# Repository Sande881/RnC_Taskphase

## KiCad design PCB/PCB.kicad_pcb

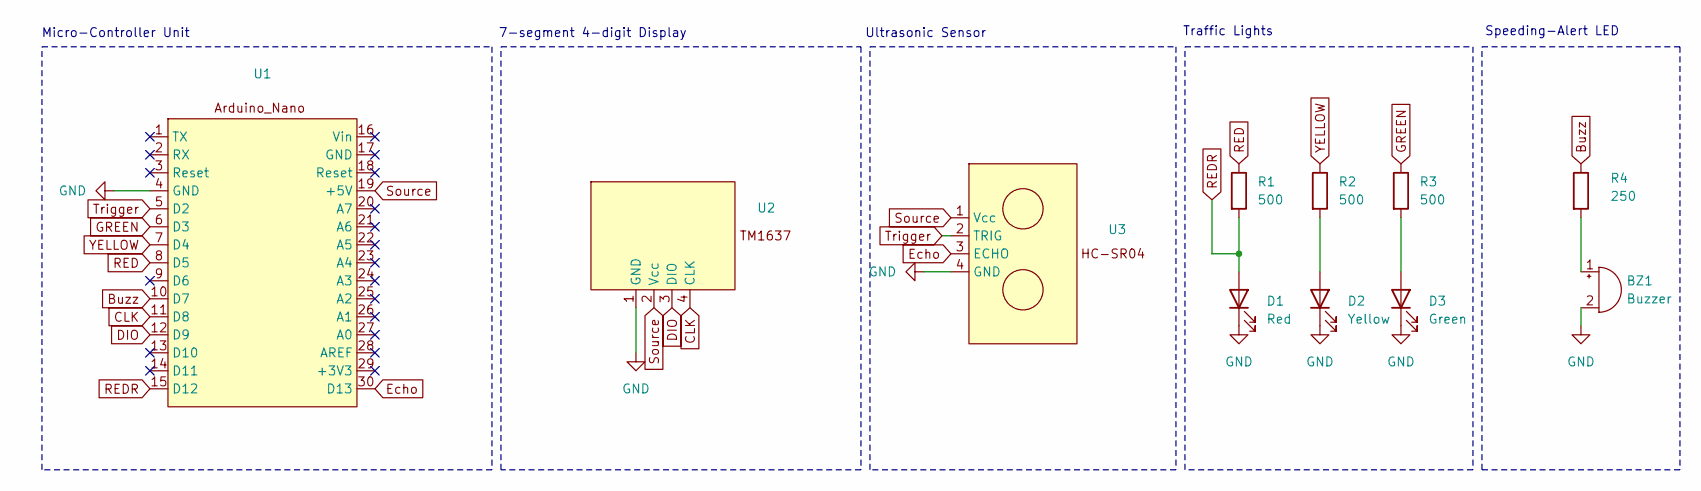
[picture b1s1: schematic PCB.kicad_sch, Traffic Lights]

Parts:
BZ1: Buzzer; Buzzer_12x9.5RM7.6
D1: Red; LED_D3.0mm_Horizontal_O1.27mm_Z2.0mm_IRGrey
D2: Yellow; LED_D3.0mm_Horizontal_O1.27mm_Z2.0mm_IRGrey
D3: Green; LED_D3.0mm_Horizontal_O1.27mm_Z2.0mm_IRGrey
R1, R2, R3: 500; R_Axial_DIN0918_L18.0mm_D9.0mm_P22.86mm_Horizontal
R4: 250; R_Axial_DIN0918_L18.0mm_D9.0mm_P22.86mm_Horizontal
U1: Arduino_Nano
U2: TM1637
U3: HC-SR04

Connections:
Buzz: R4.1, U1.10 (D7)
CLK: U1.11 (D8), U2.4 (CLK)
DIO: U1.12 (D9), U2.3 (DIO)
Echo: U1.30 (D13), U3.3 (ECHO)
GND: BZ1.2 (-), D1.1 (K), D2.1 (K), D3.1 (K), U1.4 (GND), U2.1 (GND), U3.4 (GND)
GREEN: R3.1, U1.6 (D3)
unnamed: BZ1.1 (+), R4.2
unnamed: D2.2 (A), R2.2
unnamed: D3.2 (A), R3.2
RED: R1.1, U1.8 (D5)
REDR: D1.2 (A), R1.2, U1.15 (D12)
Source: U1.19 (+5V), U2.2 (Vcc), U3.1 (Vcc)
Trigger: U1.5 (D2), U3.2 (TRIG)
YELLOW: R2.1, U1.7 (D4)

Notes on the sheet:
Traffic Lights
Micro-Controller Unit
7-segment 4-digit Display
Ultrasonic Sensor
Speeding-Alert LED

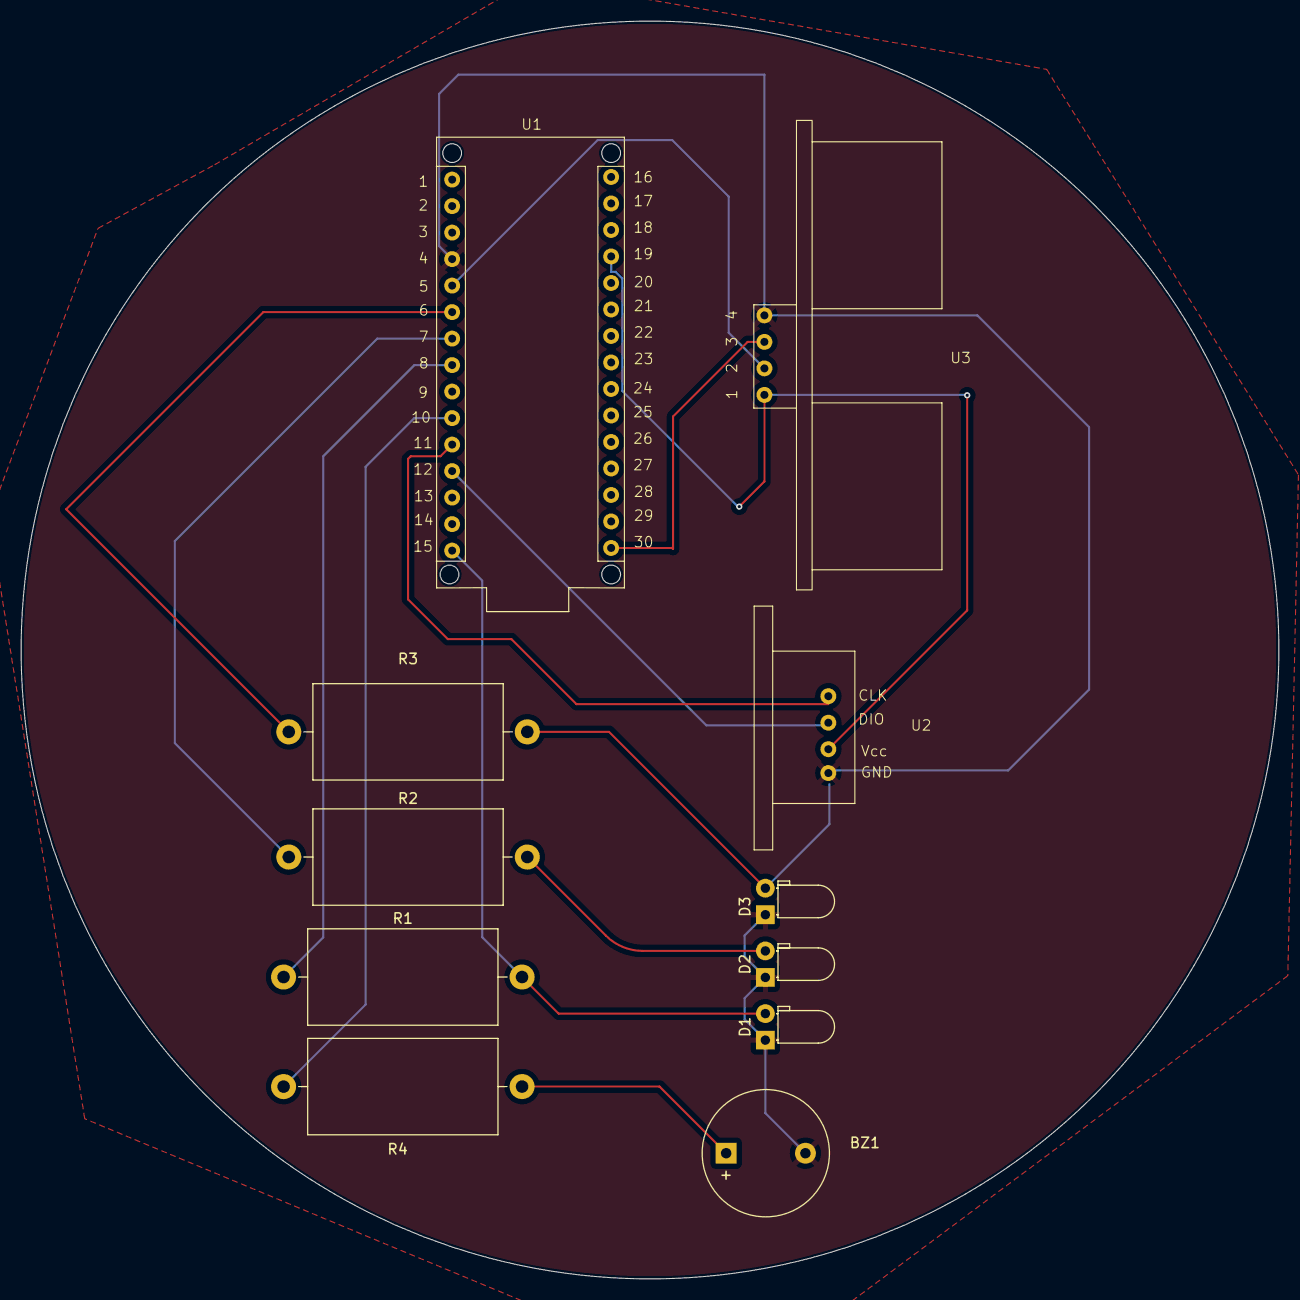
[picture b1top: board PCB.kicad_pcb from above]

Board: 2 copper layers, 120.6 x 120.6 mm, 11 parts (0 on the bottom side), 14 nets.

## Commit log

2024-12-13 PCB Files
2024-12-16 Schematic & Symbol Designs
2024-12-16 Footprint Design & Changes to Footprint/Schematics
2024-12-16 Minor Changes
2024-12-18 Arrangment of component footprints on PCB
2024-12-23 Routing & DRC of PCB
2024-12-23 Additional changes to TM1637 footprint
2024-12-23 Small changes to schematic (for DRC warnings)
2024-12-23 Gerber and Drill Files
2024-12-24 Created git-ignore file
